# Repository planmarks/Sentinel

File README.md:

# Sentinel

**Sentinel** is an open-source, low-power hardware security device by **@papathought / [muru.global](https://muru.global)**.
It is built around an STM32 microcontroller, an **Infineon OPTIGA™ Trust M** secure element, a 0.96" 128×64 OLED,
six tactile buttons, a USB‑C port and an on-board single-cell Li‑ion charger.

The same hardware family runs two different firmwares:

| Firmware | What it is | Target board | Source in this repo |
|---|---|---|---|
| **Muru Vault** | Offline password generator + AES‑256 encrypted password vault, 12‑word recovery | Sentinel **V1B** (STM32L442) | ✅ [`Vault/Firmware/`](Vault/Firmware/) |
| **Sentinel Core** `0.1.0-stm32` | Crypto cold wallet (BTC / ETH, BIP39, PIN, USB host link) | Sentinel **V1B** (STM32L442) | ❌ prebuilt `sentinel_stm32.hex` only |

---

## Hardware revisions

| | **Sentinel V1B** | **Sentinel V1C ("2MB")** |
|---|---|---|
| Folder | [`Vault/`](Vault/) | [`Cold Wallet/Hardware/`](Cold%20Wallet/Hardware/) |
| MCU | STM32L442KCU6 — Cortex‑M4F, 256 KB flash / 64 KB RAM, UFQFPN‑32 | STM32U585CIT6 — Cortex‑M33 + TrustZone, **2 MB** flash / 786 KB RAM, LQFP‑48 |
| Secure element | OPTIGA Trust M, always powered, shares I²C1 with OLED | OPTIGA Trust M on its **own I²C2 bus**, behind a **load switch** (MCU can power‑cycle it) |
| Battery fuel gauge | — | MAX17048 (I²C, alert line to MCU) |
| PCB | 2 layers, ≈ 45.3 × 73.8 mm, OLED + power switch on the back | 4 layers, ≈ 39.1 × 73.8 mm, all parts on top |
| Status | Fabricated (Gerbers in [`Vault/Sentinel-V1B Gerber.zip`](Vault/Sentinel-V1B%20Gerber.zip)), firmware running | Design in progress, 3D models / renders available, no firmware yet |
| Docs | [Hardware V1B](Docs/hardware/sentinel-v1b.md) | [Hardware V1C](Docs/hardware/sentinel-v1c.md) |

Circuits that both boards share (charger, battery protection, LDO, OLED, USB‑C, buttons, SWD) are described once in
[Common circuits](Docs/hardware/common-circuits.md).

```mermaid
flowchart LR
    USB[USB-C] -->|VBUS| CHG[MCP73833<br/>Li-ion charger]
    USB -->|D+ / D-| ESD[USBLC6 ESD] --> MCU
    CHG --> BAT[(1S Li-ion<br/>+ DW01A/FS8205A<br/>protection)]
    BAT --> SW[Slide switch] --> LDO[AP7361C<br/>3.3 V LDO]
    LDO --> MCU[STM32 MCU]
    LDO --> OLED[SSD1306<br/>128x64 OLED]
    LDO --> SE[OPTIGA Trust M]
    MCU <-->|I2C| OLED
    MCU <-->|I2C| SE
    BTN[6 buttons] --> MCU
    SWD[Tag-Connect SWD] --- MCU
```

---

## Documentation

| Topic | Document |
|---|---|
| Sentinel V1B board (STM32L442) | [Docs/hardware/sentinel-v1b.md](Docs/hardware/sentinel-v1b.md) |
| Sentinel V1C / 2MB board (STM32U585) | [Docs/hardware/sentinel-v1c.md](Docs/hardware/sentinel-v1c.md) |
| Shared circuit blocks | [Docs/hardware/common-circuits.md](Docs/hardware/common-circuits.md) |
| Muru Vault firmware internals | [Docs/firmware/muru-vault.md](Docs/firmware/muru-vault.md) |
| Muru Vault user guide | [Vault/Firmware/README.md](Vault/Firmware/README.md) |
| Sentinel Core (prebuilt wallet image) | [Docs/firmware/sentinel-core.md](Docs/firmware/sentinel-core.md) |
| Building & flashing | [Docs/firmware/flashing.md](Docs/firmware/flashing.md) |
| Original STM32 + OPTIGA migration plan | [Cold Wallet/Hardware/ARCHITECTURE.md](Cold%20Wallet/Hardware/ARCHITECTURE.md) |

---

## Tools used

| Tool | Version seen in project files |
|---|---|
| KiCad (Eeschema / Pcbnew) | 10.0.5 |
| GNU Arm Embedded (`arm-none-eabi-gcc`) | 14.3.1 (bundled with STM32CubeIDE 2.2.0) |
| STM32CubeProgrammer | used via ST‑LINK V2 over SWD |
| Python 3 | wordlist tooling in `Vault/Firmware/tools/` |
| Blender 5.2 | render scenes in `Cold Wallet/3D/`, output in `Renders/` |

## Credits

Hardware and firmware by **@papathought** — [muru.global](https://muru.global).
Third-party code: QR generator by Richard Moore (MIT, `qrcodegen.c`), public-domain SHA‑256 / AES‑256
implementations, the official BIP39 English wordlist, and an Estonian wordlist derived from
OpenSubtitles 2018 frequency data (hermitdave/FrequencyWords).

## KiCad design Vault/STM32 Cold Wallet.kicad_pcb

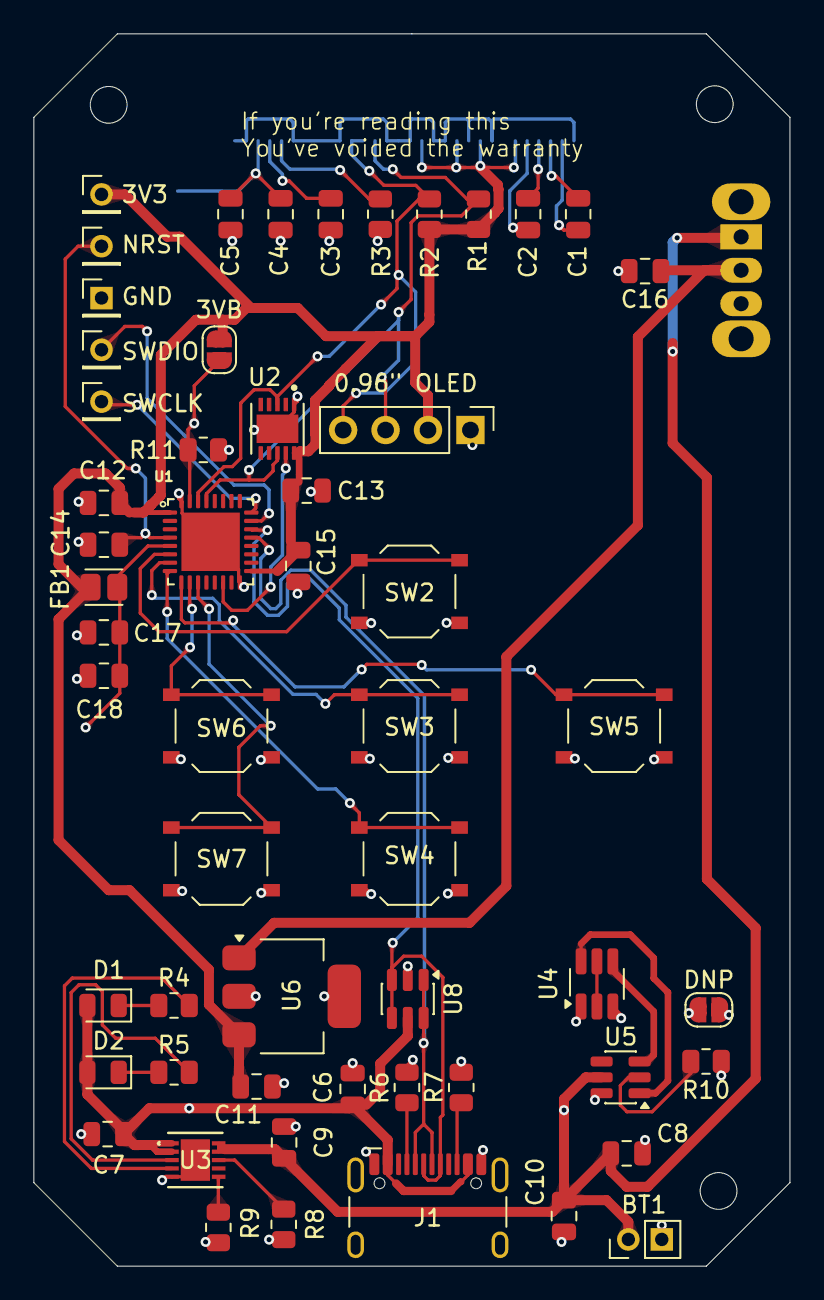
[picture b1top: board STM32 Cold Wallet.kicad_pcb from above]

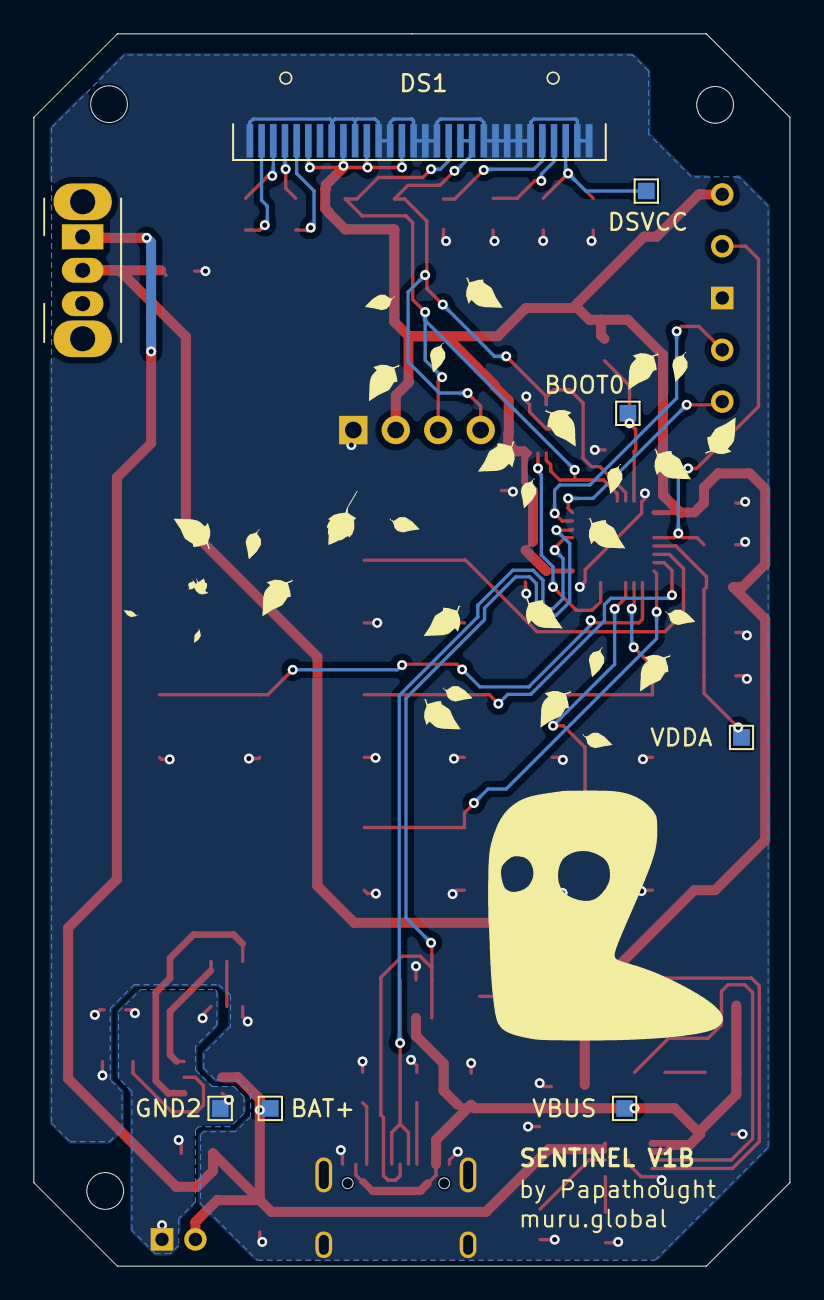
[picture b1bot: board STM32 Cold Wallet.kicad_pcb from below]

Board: 2 copper layers, 45.2 x 73.8 mm, 63 parts (8 on the bottom side), 41 nets.

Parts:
0.96" OLED: PinHeader_1x04_P2.54mm_Vertical
3V3: PinHeader_1x01_P2.00mm_Vertical
3VB: SolderJumper-2_P1.3mm_Open_RoundedPad1.0x1.5mm
BAT+: TestPoint_Pad_1.0x1.0mm
BOOT0: TestPoint_Pad_1.0x1.0mm
BT1: Battery; PinHeader_1x02_P2.00mm_Vertical
C1, C2: 2.2uF; C_0805_2012Metric
C3: 1uF; C_0805_2012Metric
C4, C8, C12, C13, C14, C15, C16, C17: 0.1uF; C_0805_2012Metric
C5: 2uF; C_0805_2012Metric
C6, C7, C9, C10, C18: 10uF; C_0805_2012Metric
C11: 22uF; C_0805_2012Metric
D1: Green LED; LED_0805_2012Metric
D2: Red LED; LED_0805_2012Metric
DNP: SolderJumper-2_P1.3mm_Open_RoundedPad1.0x1.5mm
DS1: OLED-128O064D
DSVCC: TestPoint_Pad_1.0x1.0mm
FB1: 600 Ω@100 MHz; L_Eaton_MCL2012V1
GND: PinHeader_1x01_P2.00mm_Vertical
GND2: TestPoint_Pad_1.0x1.0mm
J1: USB_C_Receptacle_USB2.0_16P; USB_C_Receptacle_HCTL_HC-TYPE-C-16P-01A
NRST: PinHeader_1x01_P2.00mm_Vertical
R1, R2: 4.7K; R_0805_2012Metric
R3: 390K; R_0805_2012Metric
R4, R5: 1K; R_0805_2012Metric
R6, R7: 5.1K; R_0805_2012Metric
R8, R11: 10K; R_0805_2012Metric
R9: 4K; R_0805_2012Metric
R10: 2K; R_0805_2012Metric
SW1: SW_SPDT On Off; SW_Slide_SPDT_Angled_CK_OS102011MA1Q
SW2: SW UP; SW_Push_1P1T_XKB_TS-1187A
SW3: SW OK; SW_Push_1P1T_XKB_TS-1187A
SW4: SW DOWN; SW_Push_1P1T_XKB_TS-1187A
SW5: SW RIGHT; SW_Push_1P1T_XKB_TS-1187A
SW6: SW LEFT; SW_Push_1P1T_XKB_TS-1187A
SW7: SW BACK; SW_Push_1P1T_XKB_TS-1187A
SWCLK: PinHeader_1x01_P2.00mm_Vertical
SWDIO: PinHeader_1x01_P2.00mm_Vertical
U1: STM32L442KCU6; QFN50P500X500X60-33N
U2: SLS32AIA010MLUSON10XTMC1; SON50P300X300X60-11N
U3: MCP73833-FCI/MF; DFN10_3x3MC_MCH
U4: FS8205A; SOT-23-6_Handsoldering
U5: DW01A; SOT-23-6
U6: AP7361C-33E; SOT-223-3_TabPin2
U8: USBLC6-2SC6; SOT-23-6
VBUS: TestPoint_Pad_1.0x1.0mm
VDDA: TestPoint_Pad_1.0x1.0mm

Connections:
+3V3: 0.96" OLED.2, 3V3.1, 3VB.2, C11.1, C12.1, C13.1, C15.1, DS1.6 (VBAT), DS1.9 (VDD), DS1.11 (BS1), DS1.14 (~RES), FB1.2, R1.1, R2.1, U1.1 (VDD), U1.17 (VDD), U2.10 (VCC), U6.3 (VO)
BAT+: BAT+.1, BT1.1 (+), C8.1, C9.1, C10.1, SW1.1 (A), U3.9, U3.10, U5.5 (VCC)
GND: 0.96" OLED.1, C3.2, C4.2, C5.2, C6.2, C7.2, C9.2, C10.2, C11.2, C12.2, C13.2, C14.2, C15.2, C16.2, C17.1, C18.1, DNP.2, DS1.1 (GND), DS1.8 (VSS), DS1.10 (BS0), DS1.12 (BS2), DS1.13 (~CS), DS1.15 (D/~C), DS1.16 (R/~W), DS1.17 (E/~RD), DS1.21 (D3), DS1.22 (D4), DS1.23 (D5), DS1.24 (D6), DS1.25 (D7), DS1.29 (VLSS), DS1.30 (GND), GND.1, J1.A1 (GND), J1.A12 (GND), J1.B1 (GND), J1.B12 (GND), J1.SH (SHIELD), R3.1, R6.2, R7.2, R8.2, R9.2, R10.2, R11.1, SW2.2 (A), SW3.2 (A), SW4.2 (A), SW5.2 (A), SW6.1 (A), SW7.2 (A), U1.16 (VSS), U1.32 (VSS), U1.33 (EXP), U2.1 (GND), U2.11 (EP), U3.5, U3.11, U4.1 (S1), U6.2 (GND), U8.2 (GND)
GND2: BT1.2 (-), C8.2, DNP.1, GND2.1, U4.3 (S2), U5.6 (GND)
I/O1: J1.A7 (D-), J1.B7 (D-), U1.21 (PA11), U8.1 (I/O1), U8.6 (I/O1)
I/O2: J1.A6 (D+), J1.B6 (D+), U1.22 (PA12), U8.3 (I/O2), U8.4 (I/O2)
NRST: C14.1, NRST.1, U1.4 (NRST)
unnamed: D1.1 (K), R4.1
unnamed: D2.1 (K), R5.1
unnamed: C2.2, DS1.5 (C1N)
unnamed: C2.1, DS1.4 (C1P)
unnamed: C1.2, DS1.2 (C2N)
unnamed: C1.1, DS1.3 (C2P)
unnamed: DS1.26 (IREF), R3.2
unnamed: C4.1, C5.1, DS1.28 (VCC), DSVCC.1
unnamed: C3.1, DS1.27 (VCOMH)
unnamed: J1.A5 (CC1), R6.1
unnamed: J1.B5 (CC2), R7.1
unnamed: R4.2, U3.4
unnamed: R5.2, U3.3
unnamed: R8.1, U3.8
unnamed: R9.1, U3.6
unnamed: C16.1, SW1.2 (B), U6.1 (VI)
unnamed: 3VB.1, BOOT0.1, R11.2, U1.31 (PH3/BOOT0)
unnamed: C17.2, C18.2, FB1.1, U1.5 (VDDA/VREF+), VDDA.1
unnamed: U4.2 (D1D2), U4.5 (D1D2)
unnamed: R10.1, U5.2 (CS)
PB0/RST: U1.14 (PB0), U2.9 (~RST)
SCL: 0.96" OLED.3, DS1.18 (D0), R1.2, U1.29 (PB6), U2.8 (SCL)
SDA: 0.96" OLED.4, DS1.19 (D1), DS1.20 (D2), R2.2, U1.30 (PB7), U2.3 (SDA)
SWBC: SW7.1 (A), U1.11 (PA5)
SWCLK: SWCLK.1, U1.24 (PA14/JTCK-SWCLK)
SWDIO: SWDIO.1, U1.23 (PA13/JTMS-SWDIO)
SWDW: SW4.1 (A), U1.8 (PA2)
SWLF: SW6.2 (A), U1.10 (PA4)
SWOK: SW3.1 (A), U1.7 (PA1)
SWRG: SW5.1 (A), U1.9 (PA3)
SWUP: SW2.1 (A), U1.6 (PA0/CK_IN)
VBUS: C6.1, C7.1, D1.2 (A), D2.2 (A), J1.A4 (VBUS), J1.A9 (VBUS), J1.B4 (VBUS), J1.B9 (VBUS), U3.1, U3.2, U8.5 (VBUS), VBUS.1
lower-FET gate: U4.4 (G2), U5.3 (OC)
upper-FET gate: U4.6 (G1), U5.1 (OD)

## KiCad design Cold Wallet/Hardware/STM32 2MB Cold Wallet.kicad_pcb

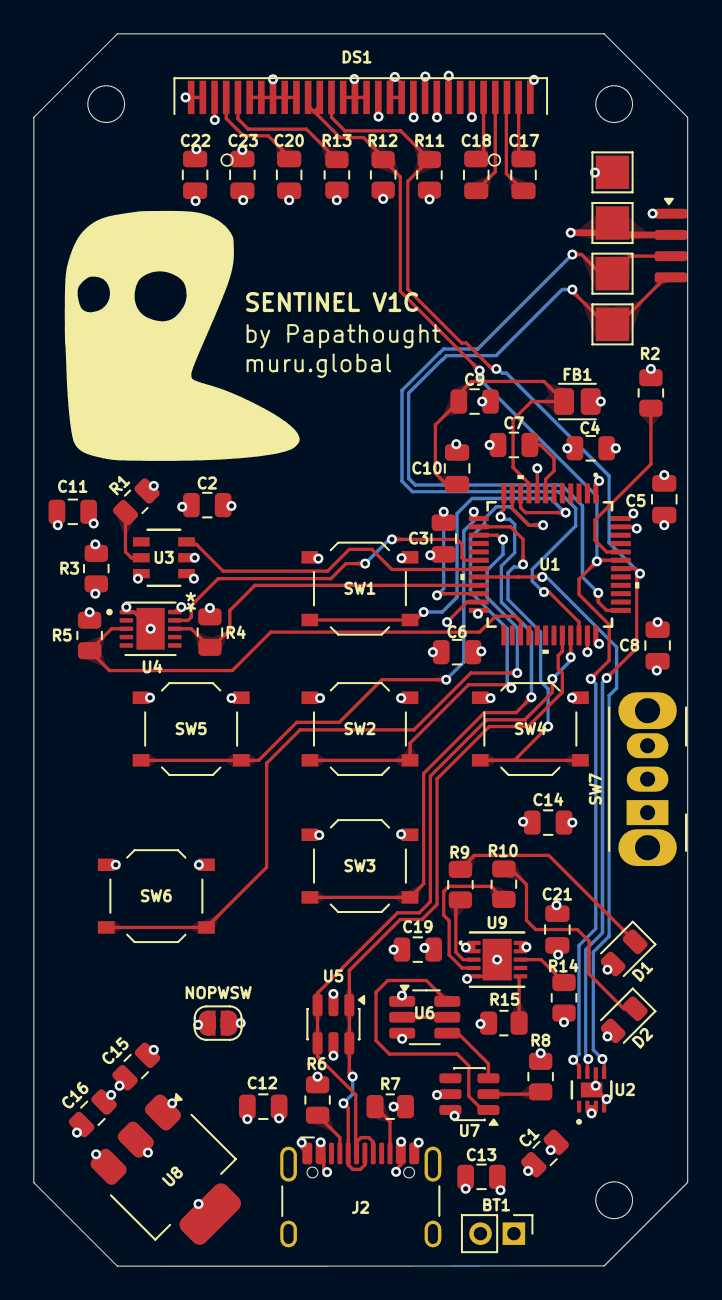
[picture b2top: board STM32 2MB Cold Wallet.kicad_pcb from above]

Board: 4 copper layers, 39.1 x 73.7 mm, 61 parts (0 on the bottom side), 46 nets.

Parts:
BT1: Battery; PinHeader_1x02_P2.00mm_Vertical
C1, C2, C4, C5, C6, C7, C8, C10, C11, C13, C15, C22: 0.1uF; C_0805_2012Metric
C3, C17, C18: 2.2µF; C_0805_2012Metric
C9, C12, C14, C19, C21: 10uF; C_0805_2012Metric
C16: 22uF; C_0805_2012Metric
C20: 1uF; C_0805_2012Metric
C23: 2uF; C_0805_2012Metric
D1: Red LED; LED_0805_2012Metric
D2: Green LED; LED_0805_2012Metric
DS1: OLED-128O064D
FB1: 600 Ω@100 MHz; L_Eaton_MCL2012V1
J2: USB_C_Receptacle_USB2.0_16P; USB_C_Receptacle_HCTL_HC-TYPE-C-16P-01A
NOPWSW: SolderJumper-2_P1.3mm_Open_RoundedPad1.0x1.5mm
R1: 60K; R_0805_2012Metric
R2, R3, R14: 10K; R_0805_2012Metric
R4, R5, R11, R12: 4.7K; R_0805_2012Metric
R6, R7: 5.1K; R_0805_2012Metric
R8: 2K; R_0805_2012Metric
R9, R10: 1K; R_0805_2012Metric
R13: 390K; R_0805_2012Metric
R15: 4K; R_0805_2012Metric
SW1: SW UP; SW_Push_1P1T_XKB_TS-1187A
SW2: SW OK; SW_Push_1P1T_XKB_TS-1187A
SW3: SW DOWN; SW_Push_1P1T_XKB_TS-1187A
SW4: SW RIGHT; SW_Push_1P1T_XKB_TS-1187A
SW5: SW LEFT; SW_Push_1P1T_XKB_TS-1187A
SW6: SW BACK; SW_Push_1P1T_XKB_TS-1187A
SW7: SW_SPDT On Off; SW_Slide_SPDT_Angled_CK_OS102011MA1Q
U1: STM32U585CIT6; LQFP48-7x7mm_STM
U2: MAX17048G+T10; 21-0168E_T822-3_MXM
U3: NCP380HSNAJAAT1G; TSOP6_1P70X3P10_ONS
U4: SLS32AIA010MLUSON10XTMC1; SON50P300X300X60-11N
U5: USBLC6-2SC6; SOT-23-6
U6: FS8205A; SOT-23-6_Handsoldering
U7: DW01A; SOT-23-6
U8: AP7361C-33E; SOT-223-3_TabPin2
U9: MCP73833-FCI/MF; DFN10_3x3MC_MCH

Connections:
+3V3: C2.2, C4.2, C5.2, C6.2, C8.2, C16.1, DS1.6 (VBAT), DS1.9 (VDD), DS1.11 (BS1), DS1.14 (~RES), FB1.2, R11.1, R12.1, U1.1 (VBAT), U1.24 (VDDA), U1.36 (VDD), U1.48 (VDD), U3.1 (IN), U8.3 (VO)
+3V3_OPTIGA: C11.1, R3.2, R4.2, R5.2, U3.6 (OUT), U4.10 (VCC)
BAT+: BT1.1 (+), C1.2, C13.1, C14.1, C21.1, NOPWSW.2, SW7.2 (B), U2.2 (CELL), U2.3 (VDD), U7.5 (VCC), U9.9, U9.10
GND: C1.1, C2.1, C3.1, C4.1, C5.1, C6.1, C7.2, C8.1, C9.1, C10.1, C11.2, C12.2, C14.2, C15.2, C16.2, C19.2, C20.2, C21.2, C22.2, C23.2, DS1.1 (GND), DS1.8 (VSS), DS1.10 (BS0), DS1.12 (BS2), DS1.13 (~CS), DS1.15 (D/~C), DS1.16 (R/~W), DS1.17 (E/~RD), DS1.21 (D3), DS1.22 (D4), DS1.23 (D5), DS1.24 (D6), DS1.25 (D7), DS1.29 (VLSS), DS1.30 (GND), J2.A1 (GND), J2.A12 (GND), J2.B1 (GND), J2.B12 (GND), J2.SH (SHIELD), R1.2, R2.1, R3.1, R6.2, R7.2, R8.2, R13.1, R14.2, R15.2, SW1.1 (A), SW2.1 (A), SW3.1 (A), SW4.1 (A), SW5.1 (A), SW6.1 (A), U1.8 (VSSA), U1.23 (VSSA), U1.35 (VSS), U1.47 (VSS), U2.4 (GND), U2.6 (QSTRT), U2.9 (EPAD), U3.2 (GND), U4.1 (GND), U4.11 (EP), U5.2 (GND), U6.1 (S1), U8.2 (GND), U9.5, U9.11
GND2: BT1.2 (-), C13.2, U6.3 (S2), U7.6 (GND)
I/O1: J2.A7 (D-), J2.B7 (D-), U1.32 (PA11), U5.1 (I/O1), U5.6 (I/O1)
I/O2: J2.A6 (D+), J2.B6 (D+), U1.33 (PA12), U5.3 (I/O2), U5.4 (I/O2)
NRST: C7.1, U1.7 (NRST)
unnamed: C9.2, C10.2, FB1.1, U1.9 (VDDA)
unnamed: D1.1 (K), R9.1
unnamed: D2.1 (K), R10.1
unnamed: C18.1, DS1.5 (C1N)
unnamed: C18.2, DS1.4 (C1P)
unnamed: C17.2, DS1.2 (C2N)
unnamed: C17.1, DS1.3 (C2P)
unnamed: DS1.26 (IREF), R13.2
unnamed: C22.1, C23.1, DS1.28 (VCC)
unnamed: C20.1, DS1.27 (VCOMH)
unnamed: J2.A5 (CC1), R6.1
unnamed: J2.B5 (CC2), R7.1
unnamed: R9.2, U9.3
unnamed: R10.2, U9.4
unnamed: R14.1, U9.8
unnamed: R15.1, U9.6
unnamed: C15.1, NOPWSW.1, SW7.3 (C), U8.1 (VI)
unnamed: R2.2, U1.44 (PH3-BOOT0)
unnamed: C3.2, U1.22 (VCAP)
unnamed: R1.1, U3.5 (ILIM)
unnamed: U6.2 (D1D2), U6.5 (D1D2)
unnamed: R8.1, U7.2 (CS)
PB0/RST: U1.18 (PB0), U4.9 (~RST)
PB1: U1.19 (PB1), U3.3 (EN)
PB2: U1.20 (PB2), U2.5 (*ALRT)
SCL: DS1.18 (D0), R11.2, U1.42 (PB6), U2.7 (SCL)
SCL2: R4.1, U1.21 (PB10), U4.8 (SCL)
SDA: DS1.19 (D1), DS1.20 (D2), R12.2, U1.43 (PB7), U2.8 (SDA)
SDA2: R5.1, U1.27 (PB14), U4.3 (SDA)
SWBC: SW6.2 (A), U1.15 (PA5)
SWDW: SW3.2 (A), U1.12 (PA2)
SWLF: SW5.2 (A), U1.13 (PA3)
SWOK: SW2.2 (A), U1.11 (PA1)
SWRG: SW4.2 (A), U1.14 (PA4)
SWUP: SW1.2 (A), U1.10 (PA0)
VBUS: C12.1, C19.1, D1.2 (A), D2.2 (A), J2.A4 (VBUS), J2.A9 (VBUS), J2.B4 (VBUS), J2.B9 (VBUS), U5.5 (VBUS), U9.1, U9.2
lower-FET gate: U6.4 (G2), U7.3 (OC)
upper-FET gate: U6.6 (G1), U7.1 (OD)

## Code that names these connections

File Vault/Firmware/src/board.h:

/* Muru Vault - board definitions for Sentinel V1B (STM32L442KCU6).
 *
 * Pin map (from STM32 Cold Wallet.net, V1B):
 *   I2C1  SCL = PB6 (AF4)   SDA = PB7 (AF4)   -> OLED SSD1306 @0x3C, OPTIGA @0x30
 *   OPTIGA reset (PB0/RST net) = PB0
 *   Buttons (active-LOW, internal pull-ups):
 *     UP=PA0  OK=PA1  DOWN=PA2  RIGHT=PA3  LEFT=PA4  BACK=PA5
 */
#ifndef BOARD_H
#define BOARD_H

#include "stm32l442xx.h"
#include <stdint.h>
#include <stddef.h>
#include <stdbool.h>

/* ---- timing ---- */
void     clock_init(void);
void     usb_clock_init(void);   /* 48 MHz USB clock (HSI48 + CRS) */
uint32_t millis(void);
void     delay_ms(uint32_t ms);

/* ---- button GPIO port/pins (all on GPIOA) ---- */
#define BTN_PORT   GPIOA
#define PIN_UP     0
#define PIN_OK     1
#define PIN_DOWN   2
#define PIN_RIGHT  3
#define PIN_LEFT   4
#define PIN_BACK   5
#define BTN_MASK   ((1u<<PIN_UP)|(1u<<PIN_OK)|(1u<<PIN_DOWN)|(1u<<PIN_RIGHT)|(1u<<PIN_LEFT)|(1u<<PIN_BACK))

#endif

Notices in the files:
README.md:
License: not yet chosen
